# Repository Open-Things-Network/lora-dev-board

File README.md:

# lora-dev-board

Uniwersalna platforma sprzętowa ułatwiająca projektowanie i testowanie urządzeń IoT wykorzystujących do komunikacji sieć LoRaWAN.

## Cele projektu

* Udostępnienie gotowego do wykorzystania projektu płytki PCB
* Dostarczenie przykładowych szablonów aplikacji pozwalających na programowanie płytki przy użyciu Arduino SDK

## Założenia

Platforma została zaprojektowana tak, aby jej zbudowanie i uruchomienie było możliwe dla hobbystów posiadających podstawowe umiejętności w zakresie budowanie układów elektronicznych oraz programowania. Zgodnie z tym  przyjęto też dodatkowe założenia: 

* Zastosowanie popularnej płytki Arduino Pro Mini z mikrokontrolerem ATmega328P
* Współpraca z najczęściej stosowanymi układami nadawczo-odbiorczymi LoRa: RFM95W lub RN2483
* Wykorzystanie różnych źródeł zasilania, w tym standardowych baterii alkalicznych, baterii litowych oraz akumulatorów litowo-polimerowych lub litowo-jonowych
* Możliwość ładowania baterii litowo-polimerowych lub litowo-jonowych z wykorzystaniem paneli fotowoltaicznych małej mocy lub poprzez gniazdo USB

## Jak zacząć?

W `templates` znajdują się szablony aplikacji, które z pewnością ułatwią realizację własnych pomysłów, a folder `projects` zawiera przykłady projektów zrealizowanych z wykorzystaniem platformy **lora-dev-board**.

Poniższe punkty zostaną wkrótce uzupełnione opisami.

* Projekt płytki: [kompletacja elementów](https://github.com/Open-Things-Network/lora-dev-board/blob/master/v1.0/README.md#lista-elementów) i budowa urządzenia
* Uruchomienie bazowej aplikacji wysyłającej informacje o stanie urządzenia

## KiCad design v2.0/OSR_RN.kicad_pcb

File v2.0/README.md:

# v2.0

# Spis treści:
1. [Opis płytki](#Opis-płytki)
2. [Bootloader](#Bootloader)
3. [Interfejs LoRaWAN](#Interfejs-LoRaWAN)
4. [Układ zasilania](#Układ-zasilania)
5. [Układ ładowania](#Układ-ładowania)
6. [Diody LED](#Diody-LED)
7. [Interfejsy komunikacyjne](#Interfejsy-komunikacyjne)
8. [Złącza zasilania](#Złącza-zasilania)
9. [Pomiar napięcia baterii](#Pomiar-napięcia-baterii)
10. [Sterowanie zasilaniem układów zewnętrznych](#Sterowanie-zasilaniem-układów-zewnętrznych)
11. [Lista elementów](#Lista-elementów)
12. [Uwagi](#Uwagi)

# Opis płytki
Platforma deweloperska oparta na mikrokontrolerze ATMega328p. Na płytce znajduje się konwerter USB-UART dzięki czemu nie są wymagane dodatkowe układy komunikacyjne do programowania.
Do komunikacji z siecią LoRaWAN służy moduł RN2483.

## Bootloader
Do mikrokontrolera wgrany jest bootloader z Arduino Pro Mini za pomocą złącz programowania ISP, dzięki czemu można przygotować oraz wgrać program przez ARDIUNO IDE lub PLATFORMIO wykorzystując konwerter USB-UART.

## Interfejs LoRaWAN
Płytka pozwala na realizację interfejsu LoRaWAN za pomocą modułu z wbudowaną obsługą stosu LoRaWAN [RN2483A](https://www.microchip.com/wwwproducts/en/RN2483) - komunikacja z modułem poprzez port szeregowy obsługiwany programowo przez piny 10 (RX) i 11 (TX) mikrokontrolera ATMega328p (odpowiednio piny 6 i 7 zgodnie z Arduino Pro Mini).

## Układ zasilania
Zastosowany regulator napięcia LDO [AP2112K-3.3TRG1](https://cdn-shop.adafruit.com/product-files/2471/AP2112.pdf).
* Maksymalne napięcie zasilania - 6V
* Minimalne napięcie zasilania - 2.5V
* Spadek napięcia dla prądu 10mA - 5mV, 300mA - 125mV, 600mA - 250mV
* Napięcie wyjściowe - 3.3V
* Prąd maksymalny - 1A

## Układ ładowania
Zastosowany kontroler ładowania akumulatorów litowo-polimerowych (Li-Po) i litowo-jonowych (Li-Ion) [MCP73831](https://www.microchip.com/wwwproducts/en/en024903#additional-features).
* Maksymalne napięcie zasilania - 6V
* Minimalne napięcie zasilania - 3.75V
* Napięcie ładowania - 4.2V
* Prąd ładowania reguluje się przez dobranie R1, dla 2k&#x2126; - 500mA, 4k&#x2126; - 250mA

## Diody LED
|Oznaczenie|Opis|
|:--------:|:---|
|T/R|dioda sygnalizująca komunikację USB-ATMEGA|
|CHR|sygnalizuje ładowanie podłączonej baterii Li-Po/Li-Ion|
|VCC|sygnalizuje obecność napięcia zasilania|
|LED|dioda do ogólnego zastosowania w aplikacji użytkownika (`USER_LED`)|

## Interfejsy komunikacyjne
Do podłączenia zewnętrznych czujników dostępne są interfejsy:
* I2C (na magistrali wlutowane są rezystory podciągające)
* port szeregowy obsługiwany programowo (z wykorzystaniem biblioteki `SoftwareSerial`) na pinach 12 (RX) i 13 (TX) ATMega328p (odpowiednio piny 8 i 9 zgodnie z Arduino Pro Mini).

## Złącza zasilania
Do płytki możemy podłączyć źródło zasilania:
* USB - złącze USB pełni funkcje zasilania płytki, źródła ładowania baterii oraz komunikację z mikrokontrolerem.
* BATTERY - złącze baterii/akumulatorów Li-Po/Li-Ion 3,6V, do złącza podłczony jest kontoler ładowania akumulatorów.
* KOSZYK - miejsce na koszyk baterii/akumulatorów Li-Po/Li-Ion o rozmiarze AA (14500) 3,6V, do złącza podłczony jest kontoler ładowania akumulatorów.
* SOLAR - może służyć jako źródło zasilania, ale najlepiej można go wykorzystać wraz z ogniwem jako źródło ładowania akumulatora. Należy wykorzystać panel o napięciu 5,5V.

> **UWAGA!** Przy wykorzystaniu baterii litowych (FR6) nie ładowalnych należy wylutować kontroler ładowania akumulatorów U4.

## Pomiar napięcia baterii
Wykorzystane wejście analogowe A0 i dzielnik napięcia R4, R5 (makro `VBAT`).

## Sterowanie zasilaniem układów zewnętrznych
Układ sterowania jest złożony z dwóch tranzystorów. Pierwszy tranzystor NPN BC817 jest wysterowany z mikrokontrolera i wykorzystany jest do kluczowania drugiego tranzystora. Tranzystor polowy z kanałem typu P pozwala na sterowanie zasilaniem zewnętrznego urządzenia. Wybór zasilania dla zewnętrznego urządzenia dokonuje się zworką JP5(BATT/VEXT). Możemy zasilać urządzenie z stabilizowanego zasilania 3.3V lub zasilanie podać z zewnątrz (lub innego punktu), wymaga to podłączenia napięcia na pad VEXT oraz rozcięcie zworki JP5 i zalutowaniu jej w pozycji EXT. Zastosowany tranzystor polowy YJL2301F pozwala na obciążenie do 2A z źródła zewnętrznego oraz 600mA z VCC (ograniczenia wynikają z parametrów LDO). 

# Lista elementów
| Oznaczenie | Element | Obudowa | Ilość na PCB |
|:-----:|:--------|:------|:--|
|KOSZYK|2915 keystone|n.d.|2|
|C1-C3;C6|100nF|0805|4|
|C4-C5|22pF|0805|2|
|C7|1uF|0805|1|
|C8|n.d.|0805|1|
|D1|LED YELLOW|0805|1|
|D2|LED GREEN|0805|1|
|D3|LED RED|0805|1|
|D4|LED BLUE|0805|1|
|D5-D6|1N5819|SOD-123|2|
|J1|u.FL|n.d.|1|
|J2;J5|PinHeader|1x04|2|
|J3|PinHeader|2x03|1|
|J4|PinHeader|1x05|1|
|J6|PinHeader|1x02|1|
|J7-J8|JST|PH-S2B|2|
|J9|USB|10118194-0001LF AMPHENOL|n.d.|1|
|Q1|YJL2301F|SOT-23|1|
|Q2|BC817|SOT-23|1|
|R1-R2;R6-R7;R9|10k|0805|5|
|R3|50R|0805|1|
|R5|33k|0805|1|
|R8;R10-R13|1k|0805|5|
|R14|4k|0805|1|
|SW1|SKRPACE010|n.d.|1|
|U1|ATMega328p-AU|TQFP-32|1|
|U2|CH340E|MSOP-10|1|
|U3|AP2112K-3.3|SOT-23-5|1|
|U4|MCP73831-2-OT|SOT-23-5|1|
|Y1|16MHz|3225|1|

# Uwagi
Na pierwszych wersjach płytki pojawił się błąd w opisie elementów Q1 i Q2. Każdy kto otrzyma taką wersję płytki zostanie o tym poinformowany.

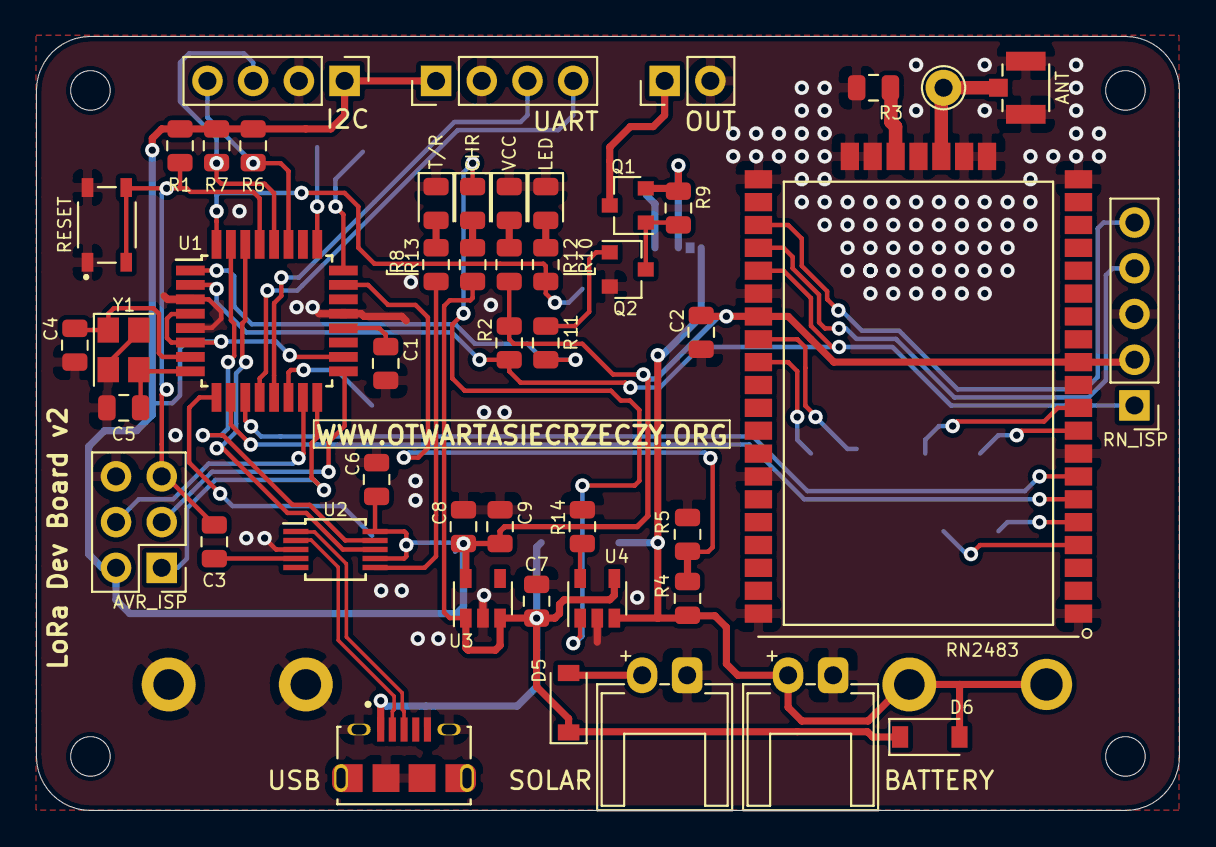
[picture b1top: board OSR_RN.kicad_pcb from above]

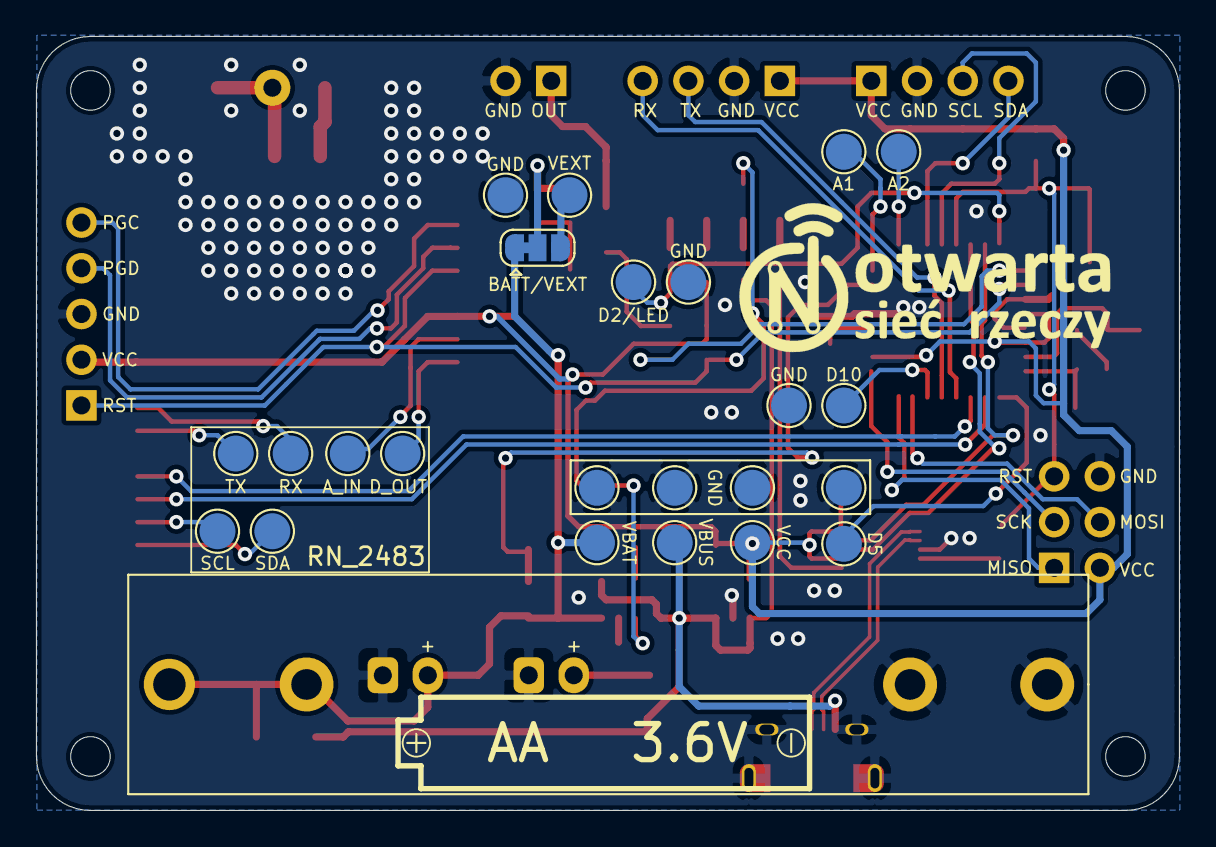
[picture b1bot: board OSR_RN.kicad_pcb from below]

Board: 2 copper layers, 63.5 x 43.0 mm, 76 parts (24 on the bottom side), 53 nets.

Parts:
A1: A1; TestPoint_Pad_D2.0mm
A2: A2; TestPoint_Pad_D2.0mm
ANT: U.FL; HRS_U.FL-R-SMT-1(10)
AVR_ISP: ISP_ATM; PinHeader_2x03_P2.54mm_Vertical
A_IN: A_IN; TestPoint_Pad_D2.0mm
BATTERY: BAT1; XH-2AW
BT1: KOSZYK; 2915_keystone
C1, C2, C3, C6: 100nF; C_0805_2012Metric
C4, C5: 22pF; C_0805_2012Metric
C7, C9: 1uF; C_0805_2012Metric
C8: NC 0805; C_0805_2012Metric
CHR: YELLOW; LED_0805_2012Metric
D2/LED: LED; TestPoint_Pad_D2.0mm
D5: D5; TestPoint_Pad_D2.0mm
D5#2, D6: 1N5819; D_SOD-123
D10: D10; TestPoint_Pad_D2.0mm
D_OUT: D_OUT; TestPoint_Pad_D2.0mm
GND: GND; TestPoint_Pad_D2.0mm
GND#2, GND#3, GND#4: GND; TestPoint_Pad_D2.0mm
H1, H2, H3, H4: M2 Hole; MountingHole_2.2mm_M2_DIN965
I2C: I2C; PinHeader_1x04_P2.54mm_Vertical
JP5: BATT/VEXT; SolderJumper-3_P1.3mm_Bridged12_RoundedPad1.0x1.5mm
LED: GREEN; LED_0805_2012Metric
OUT: OUT; PinHeader_1x02_P2.54mm_Vertical
Q1: YJL2301F; SOT-23
Q2: BC817; SOT-23
R1, R2, R6, R7, R9: 10k; R_0805_2012Metric
R3: 51; R_0805_2012Metric
R4: 100k; R_0805_2012Metric
R5: 33k; R_0805_2012Metric
R8, R10, R11, R12, R13: 1k; R_0805_2012Metric
R14: 4k; R_0805_2012Metric
RESET: RESET; SW_SKRPACE010
RN2483: RN2483; RM095
RN_ISP: ISP_RN; PinHeader_1x05_P2.54mm_Vertical
RX: RN_RX; TestPoint_Pad_D2.0mm
SCL: RN_SCL; TestPoint_Pad_D2.0mm
SDA: RN_SDA; TestPoint_Pad_D2.0mm
SOLAR: SOL1; XH-2AW
T/R: Y; LED_0805_2012Metric
TP1: ANT; TestPoint_THTPad_D2.0mm_Drill1.0mm
TP9, TP10, TP11: GND; TestPoint_Pad_D2.0mm
TX: RN_TX; TestPoint_Pad_D2.0mm
U1: ATmega328-AU; TQFP-32_7x7mm_P0.8mm
U2: CH340E; MSOP-10_3x3mm_P0.5mm
U3: AP2112K-3.3; SOT-23-5
U4: MCP73831-2-OT; SOT-23-5
UART: UART; PinHeader_1x04_P2.54mm_Vertical
USB: USB_B_Micro; AMPHENOL_10118194-0001LF
VBAT: VBAT; TestPoint_Pad_D2.0mm
VBUS: VBUS; TestPoint_Pad_D2.0mm
VCC: RED; LED_0805_2012Metric
VCC#2: VCC; TestPoint_Pad_D2.0mm
VEXT: VEXT; TestPoint_Pad_D2.0mm
Y1: 16MHz; Crystal_SMD_3225-4Pin_3.2x2.5mm

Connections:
+BATT: BATTERY.1, BT1.1, D6.2, JP5.1, R4.1, U4.3, VBAT.1
A0: R4.2, R5.1, U1.23
A1: A1.1, U1.24
A2: A2.1, U1.25
A4\SDA: I2C.4, R6.2, U1.27
A5\SCL: I2C.3, R7.2, U1.28
D2\LED: D2/LED.1, R10.2, U1.32
D3\MOSFET: R11.2, U1.1
D4\RST_RN: R2.2, RN2483.32, RN_ISP.1, U1.2
D5: D5.1, U1.9
D6\RN_TX: RN2483.6, U1.10
D7\RN_RX: RN2483.7, U1.11
D8\Rx: U1.12, UART.4
D9\Tx: U1.13, UART.3
D10: D10.1, U1.14
D11\MOSI: AVR_ISP.4, U1.15
D12\MISO: AVR_ISP.1, U1.16
D13\SCK: AVR_ISP.3, U1.17
D+: U2.1, USB.3
D-: U2.2, USB.2
DTR: C3.1, U2.4
GND: ANT.1, ANT.3, AVR_ISP.6, BATTERY.2, BT1.2, C1.1, C2.1, C4.1, C5.2, C6.2, C7.2, C8.2, C9.2, GND.1, GND#2.1, GND#3.1, GND#4.1, I2C.2, LED.1, OUT.2, Q2.2, R3.2, R5.2, R14.2, RESET.1, RN2483.1, RN2483.8, RN2483.11, RN2483.20, RN2483.21, RN2483.22, RN2483.24, RN2483.26, RN2483.27, RN2483.28, RN2483.33, RN2483.41, RN2483.47, RN_ISP.3, SOLAR.2, T/R.1, TP9.1, TP10.1, TP11.1, U1.3, U1.5, U1.21, U2.3, U3.2, U4.2, UART.2, USB.5, USB.6, VCC.1, Y1.2, Y1.4
unnamed: C1.2, U1.20
unnamed: R8.2, T/R.2
unnamed: LED.2, R10.1
unnamed: R12.1, VCC.2
unnamed: CHR.1, U4.1
unnamed: CHR.2, R13.1
unnamed: D5#2.2, SOLAR.1
unnamed: ANT.2, RN2483.23, TP1.1
unnamed: OUT.1, Q1.3
unnamed: JP5.2, Q1.2, R9.1
unnamed: JP5.3, VEXT.1
unnamed: Q1.1, Q2.3, R9.2
unnamed: Q2.1, R11.1
unnamed: R3.1, RN2483.25
unnamed: R8.1, U2.6
unnamed: R14.1, U4.5
unnamed: A_IN.1, RN2483.35
unnamed: D_OUT.1, RN2483.36
unnamed: RN2483.4, SDA.1
unnamed: RN2483.5, SCL.1
unnamed: RN2483.10, RX.1
unnamed: RN2483.9, TX.1
PGC_INT: RN2483.30, RN_ISP.5
PGD_INT: RN2483.31, RN_ISP.4
RST: AVR_ISP.5, C3.2, R1.2, RESET.2, U1.29
RxD: U1.30, U2.8
TxD: U1.31, U2.9
VBUS: C7.1, D5#2.1, D6.1, R13.2, U3.1, U3.3, U4.4, USB.1, VBUS.1
VCC: AVR_ISP.2, C2.2, C6.1, C8.1, C9.1, I2C.1, R1.1, R2.1, R6.1, R7.1, R12.2, RN2483.12, RN2483.34, RN_ISP.2, U1.4, U1.6, U1.18, U2.7, U2.10, U3.5, UART.1, VCC#2.1
XTAL1: C4.2, U1.7, Y1.1
XTAL2: C5.1, U1.8, Y1.3

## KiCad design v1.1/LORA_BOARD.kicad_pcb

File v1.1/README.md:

# v1.1

Zmiany w stosunku do płytki w wersji [v1.0](../v1.0/README.md):
* poprawiony sposób montażu elementu Q2,
* zmiana opisu włącznika (element SW1).

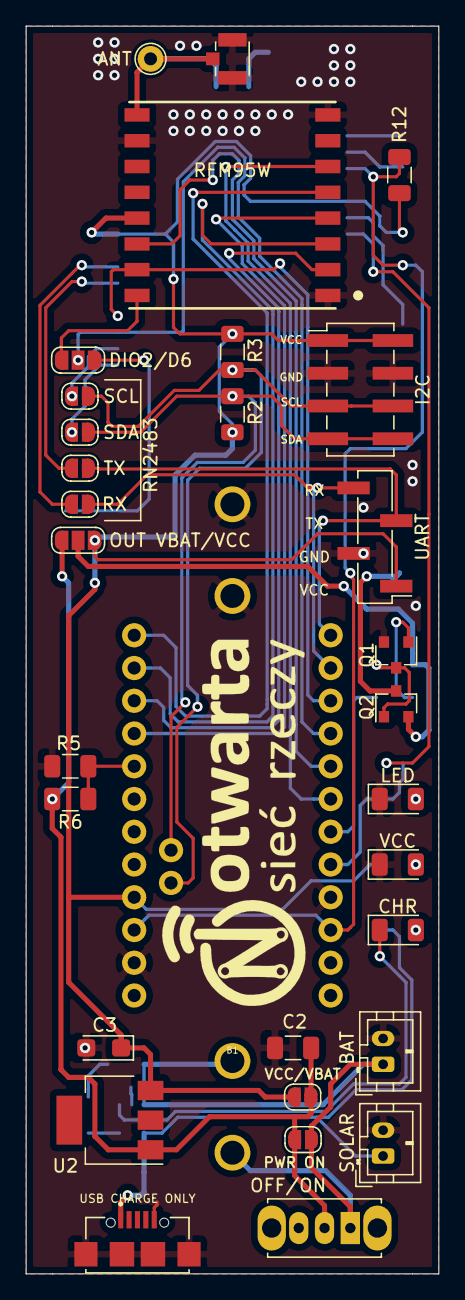
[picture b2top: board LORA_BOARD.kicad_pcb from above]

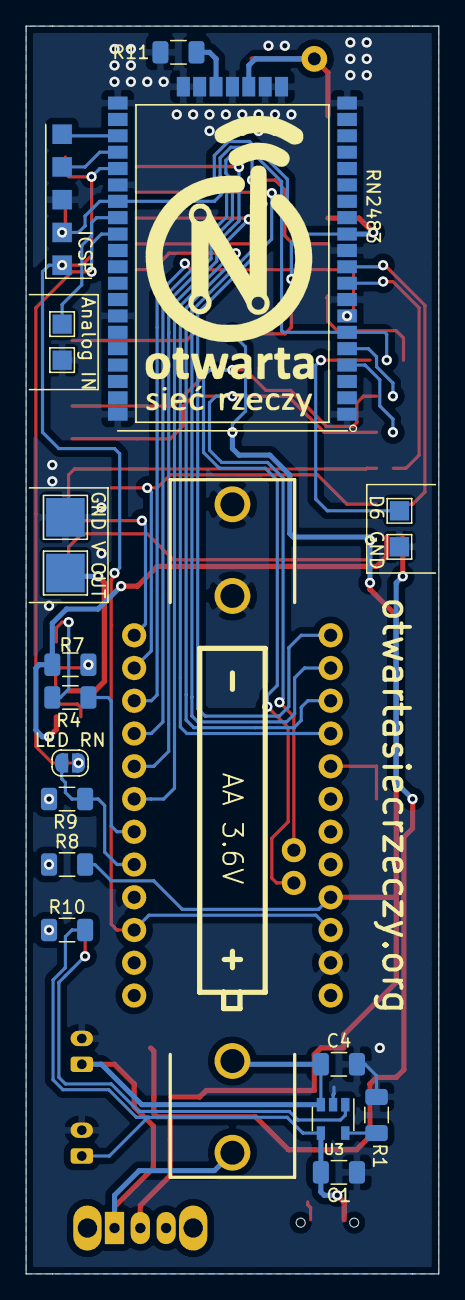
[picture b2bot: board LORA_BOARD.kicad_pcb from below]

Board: 2 copper layers, 32.0 x 96.8 mm, 53 parts (20 on the bottom side), 42 nets.

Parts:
ANT: ANT; TestPoint_THTPad_D2.0mm_Drill1.0mm
B1: ARDUINO; ARDUINO_PRO_MINI
BAT: PH; JST_PH_B2B-PH-K_1x02_P2.00mm_Vertical
BT1: AA 3.6V; BATTERY-AA-KIT
C1, C4: 4,7uF; C_1206_3216Metric
C2: 100nF; C_1206_3216Metric
C3: 22uF; CP_EIA-3216-18_Kemet-A
CHR: CHR; LED_1206_3216Metric
D6: PWM; TestPoint_Pad_1.5x1.5mm
DIO2/D6: PWM/DIO2; SolderJumper-3_P1.3mm_Open_RoundedPad1.0x1.5mm
GND: GND; TestPoint_Pad_1.5x1.5mm
GND#2: GND; TestPoint_Pad_3.0x3.0mm
GND#3: GND; TestPoint_Pad_1.5x1.5mm
J2: U.FL; HRS_U.FL-R-SMT-1(10)
J3: UART; PinHeader_1x04_P2.54mm_Vertical_SMD_Pin1Left
J4: I2C; PinHeader_2x04_P2.54mm_Vertical_SMD
J5: ICSP; CON_SMD_01x05
LED: LED; LED_1206_3216Metric
LED RN: LED; SolderJumper-2_P1.3mm_Open_RoundedPad1.0x1.5mm
OFF/ON: PWR ON; SW_Slide_1P2T_CK_OS102011MS2Q
OUT VBAT/VCC: VCC/VBAT; SolderJumper-3_P1.3mm_Open_RoundedPad1.0x1.5mm
PWR ON: PWR ON; SolderJumper-2_P1.3mm_Open_RoundedPad1.0x1.5mm
Q1: BC817; SOT-23
Q2: DMG2301L; SOT-23
R1: 4k; R_1206_3216Metric
R2, R3, R7, R12: 10k; R_1206_3216Metric
R4, R8, R9: 1k; R_1206_3216Metric
R5: 100k; R_1206_3216Metric
R6: 33k; R_1206_3216Metric
R10: 470; R_1206_3216Metric
R11: 51; R_1206_3216Metric
RFM95W: RFM95W; XCVR_RFM95W-868S2
RN2483: RN2483; RM095
RX: RX; SolderJumper-2_P1.3mm_Open_RoundedPad1.0x1.5mm
Ref**: Val**; OSR_Vertical_15x25
Ref**#2: Val**; OSR_Horizontal_12x29
SCL: SCL; SolderJumper-2_P1.3mm_Open_RoundedPad1.0x1.5mm
SDA: SDA; SolderJumper-2_P1.3mm_Open_RoundedPad1.0x1.5mm
SOLAR: PH; JST_PH_B2B-PH-K_1x02_P2.00mm_Vertical
TP1: Analog IN; TestPoint_Pad_1.5x1.5mm
TX: TX; SolderJumper-2_P1.3mm_Open_RoundedPad1.0x1.5mm
U2: TS2940-3.3; SOT-223
U3: MCP73831-2-OT; SOT-23-5
USB CHARGE ONLY: 629105136821; WE_629105136821
V OUT: +V; TestPoint_Pad_3.0x3.0mm
VCC: PWR; LED_1206_3216Metric
VCC/VBAT: VBAT; SolderJumper-2_P1.3mm_Open_RoundedPad1.0x1.5mm

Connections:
A0: B1.17, R5.2, R6.1
ANT: ANT.1, J2.2, RFM95W.9, RN2483.23
D2: B1.5, LED RN.2, R9.1
D3: B1.6, R4.2
D4: B1.7, RFM95W.6
D5: B1.8, RFM95W.14
D6: B1.9, DIO2/D6.2, RN2483.6
D7: B1.10, RFM95W.15, RN2483.7
D10: B1.13, RFM95W.5
D11: B1.14, RFM95W.3
D12: B1.15, RFM95W.2
D13: B1.16, RFM95W.4
GND: B1.4, B1.23, BAT.2, BT1.GND@, C1.2, C2.2, C3.2, C4.2, GND.1, GND#2.1, GND#3.1, J2.1, J2.3, J3.2, J4.3, J4.4, J5.3, LED.1, Q1.2, R1.2, R6.2, R11.2, RFM95W.1, RFM95W.8, RFM95W.10, RN2483.1, RN2483.8, RN2483.11, RN2483.20, RN2483.21, RN2483.22, RN2483.24, RN2483.26, RN2483.27, RN2483.28, RN2483.33, RN2483.41, RN2483.47, SOLAR.2, U2.2, U3.2, USB CHARGE ONLY.5, USB CHARGE ONLY.S1, USB CHARGE ONLY.S2, USB CHARGE ONLY.S3, USB CHARGE ONLY.S4, VCC.1
unnamed: BAT.1, BT1.PWR@, C4.1, OFF/ON.1, PWR ON.1, U3.3
unnamed: R8.2, VCC.2
unnamed: LED.2, R9.2
unnamed: CHR.2, R10.2
unnamed: LED RN.1, RN2483.36
unnamed: DIO2/D6.1, RFM95W.16
unnamed: D6.1, DIO2/D6.3
unnamed: RN2483.10, RX.2
unnamed: RN2483.9, TX.1
unnamed: RN2483.5, SCL.2
unnamed: RN2483.4, SDA.1
unnamed: OUT VBAT/VCC.2, Q2.2, R7.1
unnamed: R11.1, RN2483.25
unnamed: RN2483.35, TP1.1
unnamed: Q1.1, R4.1
unnamed: Q1.3, Q2.1, R7.2
unnamed: Q2.3, V OUT.1
unnamed: R1.1, U3.5
PGC_INT: J5.5, RN2483.30
PGD_INT: J5.4, RN2483.31
RST: B1.3, B1.22, J5.1, R12.1, RN2483.32
RX: B1.11, J3.4, RX.1
SCL: B1.A5, J4.5, J4.6, R3.2, SCL.1
SDA: B1.A4, J4.7, J4.8, R2.2, SDA.2
STAT: CHR.1, U3.1
TX: B1.12, J3.3, TX.2
VBAT: C2.1, OFF/ON.2, OUT VBAT/VCC.1, PWR ON.2, R5.1, U2.1, VCC/VBAT.1
VCC: B1.21, C3.1, J3.1, J4.1, J4.2, J5.2, OUT VBAT/VCC.3, R2.1, R3.1, R8.1, R12.2, RFM95W.13, RN2483.12, RN2483.34, U2.3, VCC/VBAT.2
VDD: C1.1, R10.1, SOLAR.1, U3.4, USB CHARGE ONLY.1

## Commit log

2020-04-22 Add templates
2020-04-22 Create LICENSE
2020-04-23 Update templates
2020-04-26 EDIT
2020-04-26 README Update
2020-04-26 LORA_BOARD.pdf update
2020-05-05 Add pcb-overview.png
2020-05-07 Update README.md
    1. Spis treści
    2. Przeniesione instrukcje dla minimalnej wersji
    3. Przeprojektowana lista elementów
2020-05-07 Update README.md
    Poprawiony Spis treści
2020-05-07 Update README.md
    1.Mała poprawka w liście elementów
    2.Wpisanie przeznaczenia zworek
2020-05-18 dodanie wersji v1.1
2020-05-21 Poprawienie opisu włącznika zasilania; Dodanie plików produkcyjnych GERBER.
2020-05-21 Update file
2020-06-08 Update README.md
    Uzupełnienie: "Sterowanie zasilaniem układów zewnętrznych"
2020-06-17 Poprawienie LORA_BOARD.pdf.
2020-08-02 UPDATE "..układów zewnętrznych"
2020-10-02 Rename lorawan-OTN-dev-board.ino to smogometr-dev-board.ino
2020-12-30 v2.0
2021-01-04 -Zmiany w schemacie: -Usunięte połączenia z RN do header'ów, zastąpione TestPoint'ami -Aktualizacja projektu płytki
2021-01-14 Przeorganizowanie ścieżek.
2021-02-16 SCH: -kosmetyka PCB: -Zmiana złącz baterii i panelu fotowoltaicznego na raster 2.5mm (JST). -Zmiana obudowy diod zabezpieczających. -Kosmetyka
2021-02-19 Zmiana złącza USB Zmiana złącz baterii i panelu fotowoltaicznego Dodanie opisów Kosmetyka
2021-02-19 Poprawki w schemacie PDF.
2021-02-20 Uzupełnienie bibliotek, footprintów oraz modeli 3D
2021-03-17 v2.2
2021-03-20 README UPDATE SCHEMAT.PDF UPDATE
2021-03-20 READ UPDATE
2024-11-25 Add battery voltage measurement
2025-03-10 Add case files & readme.
2025-08-01 Added resetting after every boot. Prevents hang on initialization of RN chip.
